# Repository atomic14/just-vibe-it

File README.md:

# Vibetastic - Single Key Keyboard

*Click the image above to watch the demo video*

## Overview

A very silly but functional single-key keyboard - perfect for vibe coding! This project combines interesting hardware design choices with AI-assisted firmware development.

## Key Features

- **Dual Power Management**: Uses TPS2117 for clean switching between battery and USB power with controlled slew rate
- **Versatile Switch Compatibility**: Custom PCB footprint supports both low-profile and full-height Cherry MX switches
- **Stabilizer Support**: Full-height keycaps can use stabilizers for improved feel and reduced wobble
- **AI-Coded Firmware**: The entire codebase was developed through AI collaboration without manual code review

## Hardware Highlights

The PCB incorporates several thoughtful design decisions:
- TPS2117 power switch controller enables high capacitance loads without violating USB specifications
- Hybrid Cherry MX footprint accommodates both switch types (though stabilizers only work with full-height switches)
- Clean power management replaces traditional MOSFET/diode circuits

## Project Structure

- `/firmware/` - PlatformIO-based embedded firmware
- `/hardware/` - KiCad PCB design files and component libraries

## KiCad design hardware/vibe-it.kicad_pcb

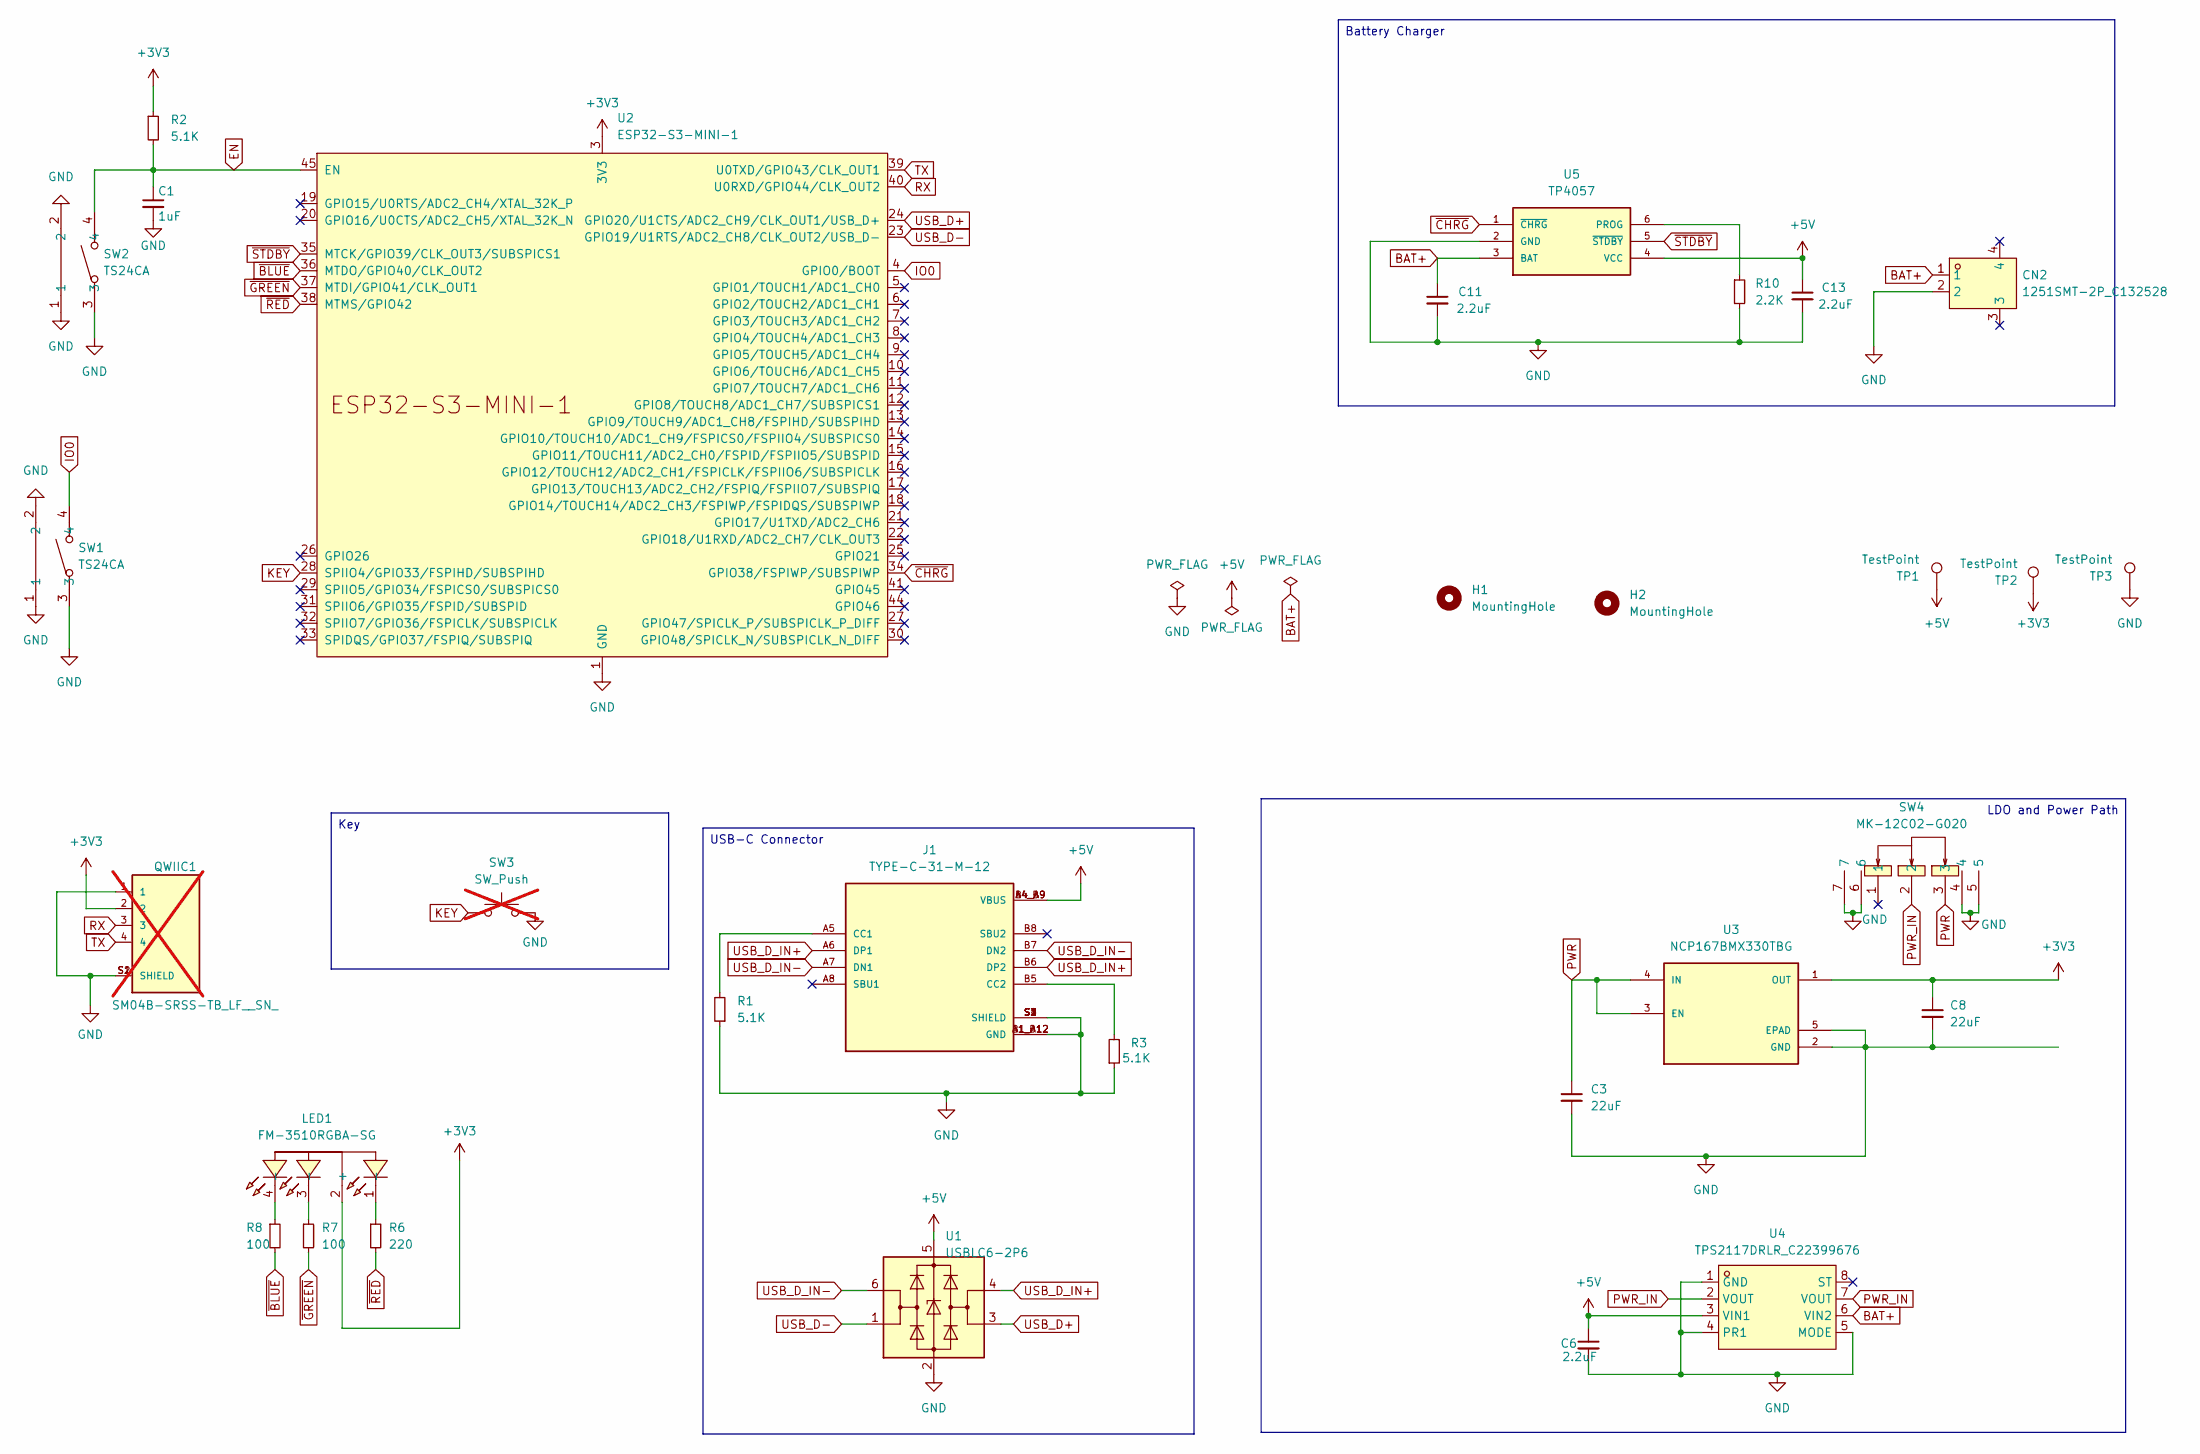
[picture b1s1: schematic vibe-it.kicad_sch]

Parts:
C1: 1uF; C_0603_1608Metric
C3, C8: 22uF; C_0603_1608Metric
C6: 2.2uF; C_0603_1608Metric; Mfg Part # test
C11, C13: 2.2uF; C_0603_1608Metric
CN2: 1251SMT-2P_C132528; CONN-SMD_1251SMT-2P; LCSC Part C132528
H1, H2: MountingHole; MountingHole_2.2mm_M2
J1: TYPE-C-31-M-12; HRO_TYPE-C-31-M-12; PARTREV 2020.12.08
LED1: FM-3510RGBA-SG; LED-SMD_FM-3510RGBA-SG; LCSC Part C727903
QWIIC1: SM04B-SRSS-TB_LF__SN_; JST_SM04B-SRSS-TB_LF__SN_; not fitted
R1, R2, R3: 5.1K; R_0603_1608Metric
R6: 220; R_0603_1608Metric
R7, R8: 100; R_0603_1608Metric
R10: 2.2K; R_0603_1608Metric
SW1, SW2: TS24CA; SW-SMD_TS24CA; LCSC Part C393942
SW3: SW_Push; Cherry-combined-low-mx; not fitted
SW4: MK-12C02-G020; SW-SMD_MK-12C02-G020; LCSC Part C963206
TP1, TP2, TP3: TestPoint; TestPoint_Pad_D2.0mm
U1: USBLC6-2P6; SOT-666
U2: ESP32-S3-MINI-1
U3: NCP167BMX330TBG; VREG_NCP167BMX330TBG; PARTREV 5
U4: TPS2117DRLR_C22399676; SOT-583-8; LCSC Part C22399676
U5: TP4057; SOT-23-6

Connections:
+3V3: C8.1, LED1.2 (+), QWIIC1.2, R2.1, TP2.1, U2.3 (3V3), U3.1 (OUT)
+5V: C6.1, C13.1, J1.A4_B9 (VBUS), J1.B4_A9 (VBUS), TP1.1, U1.5 (VBUS), U4.3 (VIN1), U5.4 (VCC)
BAT+: C11.1, CN2.1, U4.6 (VIN2), U5.3 (BAT)
EN: C1.1, R2.2, SW2.4, U2.45 (EN)
GND: C1.2, C3.2, C6.2, C8.2, C11.2, C13.2, CN2.2, J1.A1_B12 (GND), J1.B1_A12 (GND), J1.S1 (SHIELD), J1.S2 (SHIELD), J1.S3 (SHIELD), J1.S4 (SHIELD), QWIIC1.1, QWIIC1.S1 (SHIELD), QWIIC1.S2 (SHIELD), R1.1, R3.1, R10.2, SW1.1, SW1.2, SW1.3, SW2.1, SW2.2, SW2.3, SW3.2, SW4.4, SW4.5, SW4.6, SW4.7, TP3.1, U1.2 (GND), U2.1 (GND), U2.2 (GND), U2.42 (GND), U2.43 (GND), U2.46 (GND), U2.47 (GND), U2.48 (GND), U2.49 (GND), U2.50 (GND), U2.51 (GND), U2.52 (GND), U2.53 (GND), U2.54 (GND), U2.55 (GND), U2.56 (GND), U2.57 (GND), U2.58 (GND), U2.59 (GND), U2.60 (GND), U2.61 (GND), U2.62 (GND), U2.63 (GND), U2.64 (GND), U2.65 (GND), U3.2 (GND), U3.5 (EPAD), U4.1 (GND), U4.4 (PR1), U4.5 (MODE), U5.2 (GND)
IO0: SW1.4, U2.4 (GPIO0/BOOT)
KEY: SW3.1, U2.28 (SPIIO4/GPIO33/FSPIHD/SUBSPIHD)
unnamed: J1.A5 (CC1), R1.2
unnamed: J1.B5 (CC2), R3.2
unnamed: LED1.1 (-), R6.1
unnamed: LED1.3 (-), R7.1
unnamed: LED1.4 (-), R8.1
unnamed: R10.1, U5.6 (PROG)
PWR: C3.1, SW4.3, U3.3 (EN), U3.4 (IN)
PWR_IN: SW4.2, U4.2 (VOUT), U4.7 (VOUT)
RX: QWIIC1.3, U2.40 (U0RXD/GPIO44/CLK_OUT2)
TX: QWIIC1.4, U2.39 (U0TXD/GPIO43/CLK_OUT1)
USB_D+: U1.3 (I/O2), U2.24 (GPIO20/U1CTS/ADC2_CH9/CLK_OUT1/USB_D+)
USB_D-: U1.1 (I/O1), U2.23 (GPIO19/U1RTS/ADC2_CH8/CLK_OUT2/USB_D-)
USB_D_IN+: J1.A6 (DP1), J1.B6 (DP2), U1.4 (I/O2)
USB_D_IN-: J1.A7 (DN1), J1.B7 (DN2), U1.6 (I/O1)
~BLUE: R8.2, U2.36 (MTDO/GPIO40/CLK_OUT2)
~CHRG: U2.34 (GPIO38/FSPIWP/SUBSPIWP), U5.1 (~CHRG)
~GREEN: R7.2, U2.37 (MTDI/GPIO41/CLK_OUT1)
~RED: R6.2, U2.38 (MTMS/GPIO42)
~STDBY: U2.35 (MTCK/GPIO39/CLK_OUT3/SUBSPICS1), U5.5 (~STDBY)

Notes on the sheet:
LDO and Power Path
Battery Charger
USB-C Connector
Key

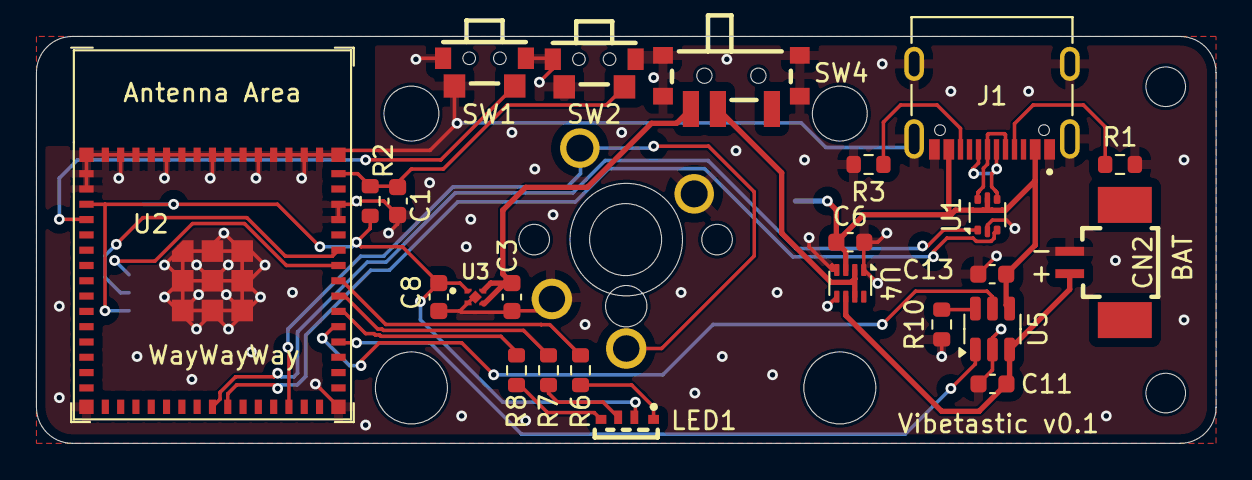
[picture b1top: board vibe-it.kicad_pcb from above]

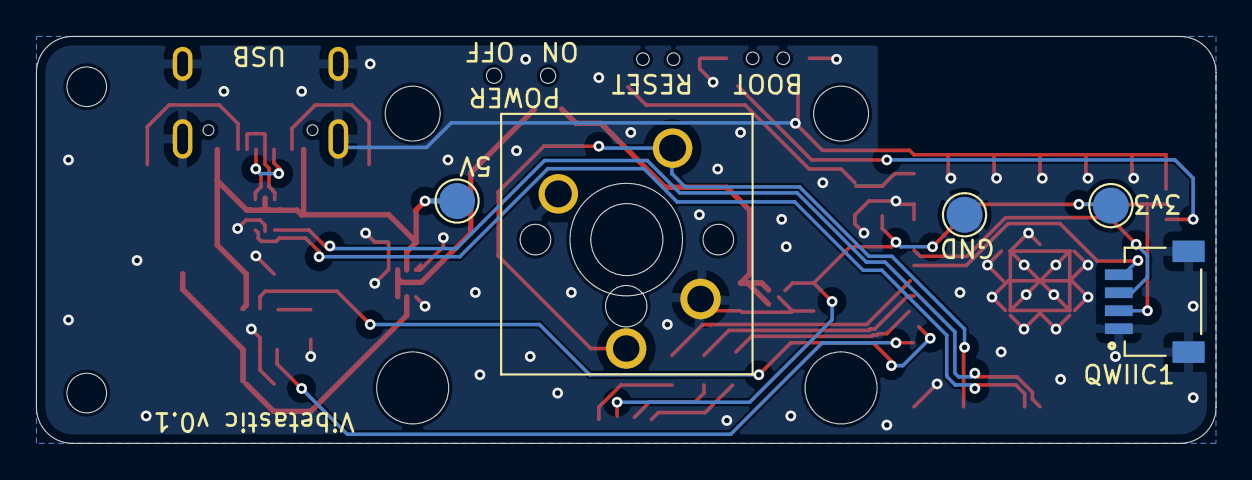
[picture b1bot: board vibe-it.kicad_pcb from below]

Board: 2 copper layers, 65.5 x 22.6 mm, 31 parts (5 on the bottom side), 26 nets.

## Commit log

2025-07-04 Initial commit - fully vibed up!
2025-07-04 Adds action
2025-07-04 Fix action
2025-07-04 Adds build badge
